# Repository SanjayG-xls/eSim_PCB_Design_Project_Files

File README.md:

<p align="center">
  
</p>

<p align="center">

</p>

## 📋 Table of Contents

- [About the Project](#-about-the-project)
- [STM32F4VE Hardware Overview](#-stm32f4ve-hardware-overview)
- [Software & Toolchain](#-software--toolchain)
- [Hardware Specifications](#-hardware-specifications--features)
- [PCB Stackup & Layer Configuration](#-pcb-stackup--layer-configuration)
- [3D Board Renders](#-3d-board-renders)
- [Schematic Design](#-schematic-design)
- [PCB Layout Views](#-pcb-layout-views)
- [Design Verification](#-design-verification)
- [How to Use](#-how-to-use-this-repository)
- [Video Walkthrough](#-video-walkthrough)
- [Attribution](#-attribution)

## 🔬 About the Project

> 🏛️ **FOSSEE Autumn Internship 2026 — Screening Task**
>
> 
> 
> 
> 
> 

This repository contains the **complete printed circuit board design and schematic files** for an STM32F4VE microcontroller development board. The design was developed as part of the screening task for the **FOSSEE Autumn Internship program in 2026** at **IIT Bombay**.

The core of this board is the high-performance **STM32F407VET6** IC, providing a robust hardware platform for advanced microelectronics and circuit design applications. The board features a **black solder mask** to replicate standard commercial STM development boards, with **custom silkscreen graphics** featuring the official FOSSEE logo, the STM logo, and the designer's name.

## 🧠 STM32F4VE Hardware Overview

The **STM32F4VE** (STM32F407VET6) is a powerful, high-performance **ARM Cortex-M4** core device widely used in embedded systems due to its balance of processing power, memory, and rich peripheral set.

<table>
<tr>
<td width="50%">

### ⚙️ Core Specifications

| Parameter | Value |
|:---|:---|
| **Processor** | ARM 32-bit Cortex-M4 with FPU |
| **Max Frequency** | 168 MHz |
| **Flash Memory** | 512 KB |
| **SRAM** | 192 KB + 4 KB backup |
| **Operating Voltage** | 1.8V – 3.6V |
| **Package** | LQFP-100 |

</td>
<td width="50%">

### 🔌 Advanced Peripherals

| Interface | Count |
|:---|:---|
| **I2C** | Up to 3x |
| **SPI** | Up to 3x |
| **I2S** | Up to 2x |
| **USART / UART** | 4x USART + 2x UART |
| **CAN Bus** | 2x |
| **SDIO** | 1x |

</td>
</tr>
</table>

<p align="center">
  
  <br/>
  <sub><b>STM32F407VET6 — Reference Development Board</b></sub>
</p>

## 🛠️ Software & Toolchain

<table>
<tr>
  <td align="center" width="160">
    
    <br/><sub><b>Schematic Design</b></sub>
  </td>
  <td align="center" width="160">
    
    <br/><sub><b>PCB Layout</b></sub>
  </td>
  <td align="center" width="160">
    
    <br/><sub><b>3D Models / Symbols / Footprints</b></sub>
  </td>
  <td align="center" width="160">
    
    <br/><sub><b>Manufacturing Rules</b></sub>
  </td>
</tr>
</table>

> 📌 **Note:** Schematic design was done in **eSim 2.5**, with PCB layout handled by **KiCad 6** (integrated via eSim). All component libraries — 3D models, schematic symbols, and footprints — were sourced from **SnapEDA**.

## ⚡ Hardware Specifications & Features

> 🔧 **Key Features at a Glance**
>
> 
> 
> 
> 
> 

<table>
<tr>
  <td width="50%" valign="top">

  ### 🎛️ Board Features

  | Feature | Description |
  |:---|:---|
  | **Microcontroller** | STM32F407VET6 high-speed MCU |
  | **Power Management** | 3.3V power routing with CR12 backup battery |
  | **Connectivity** | Micro USB port, SD Card reader |
  | **Headers** | Extensive connector headers for GPIO access |
  | **Timing** | Onboard oscillators for accurate clocking |
  | **User Interface** | Integrated switches and status LEDs |

  </td>
  <td width="50%" valign="top">

  ### 🏭 Manufacturing Specs

  | Parameter | Value |
  |:---|:---|
  | **Layer Count** | 4-Layer PCB |
  | **Manufacturer** | JLCPCB (base model rules) |
  | **Solder Mask** | Black (commercial-grade) |
  | **Silkscreen** | Custom graphics (FOSSEE + STM logos) |
  | **ERC Status** | ✅ Passed (0 errors) |
  | **DRC Status** | ✅ Passed (0 errors) |

  </td>
</tr>
</table>

## 🧱 PCB Stackup & Layer Configuration

The board is routed as a **4-layer PCB**, specifically configured to comply with **JLCPCB base model** manufacturing rules.

<table>
<tr>
  <th align="center">Layer</th>
  <th align="center">Name</th>
  <th align="center">Function</th>
</tr>
<tr>
  <td align="center">🔴 Layer 1</td>
  <td align="center"><b>Front (F.Cu)</b></td>
  <td>Signal routing and ground pour</td>
</tr>
<tr>
  <td align="center">🟡 Layer 2</td>
  <td align="center"><b>Inner 1 (In1.Cu)</b></td>
  <td>Dedicated ground plane</td>
</tr>
<tr>
  <td align="center">🟢 Layer 3</td>
  <td align="center"><b>Inner 2 (In2.Cu)</b></td>
  <td>Dedicated 3.3V power plane</td>
</tr>
<tr>
  <td align="center">🔵 Layer 4</td>
  <td align="center"><b>Back (B.Cu)</b></td>
  <td>Ground plane</td>
</tr>
</table>

<table>
<tr>
  <td align="center" width="50%">
    <b>📐 Layer 1 — Front Copper</b><br/>
    
  </td>
  <td align="center" width="50%">
    <b>📐 Layer 2 — Inner Ground Plane</b><br/>
    
  </td>
</tr>
<tr>
  <td align="center" width="50%">
    <b>📐 Layer 3 — Inner Power Plane (3.3V)</b><br/>
    
  </td>
  <td align="center" width="50%">
    <b>📐 Layer 4 — Back Copper</b><br/>
    
  </td>
</tr>
</table>

<details>
<summary><b>🔍 Click to view individual PCB layer renders</b></summary>
<br/>

<table>
<tr>
  <td align="center" width="50%">
    <b>Front Layer PCB</b><br/>
    
  </td>
  <td align="center" width="50%">
    <b>Back Layer PCB</b><br/>
    
  </td>
</tr>
<tr>
  <td align="center" width="50%">
    <b>Inner Layer 1 (In1.Cu)</b><br/>
    
  </td>
  <td align="center" width="50%">
    <b>Inner Layer 2 (In2.Cu)</b><br/>
    
  </td>
</tr>
</table>

<table>
<tr>
  <td align="center" width="50%">
    <b>All Layers Combined</b><br/>
    
  </td>
  <td align="center" width="50%">
    <b>All ICs Highlighted</b><br/>
    
  </td>
</tr>
</table>

</details>

## 🖼️ 3D Board Renders

<table>
<tr>
  <td align="center" width="50%">
    <b>🔝 Front View — 3D Render</b><br/>
    
  </td>
  <td align="center" width="50%">
    <b>🔽 Back View — 3D Render</b><br/>
    
  </td>
</tr>
<tr>
  <td align="center" width="50%">
    <b>📐 Side View — 3D Render</b><br/>
    
  </td>
  <td align="center" width="50%">
    <b>📐 Side Down View — 3D Render</b><br/>
    
  </td>
</tr>
</table>

<details>
<summary><b>🔍 Click to view additional 3D renders</b></summary>
<br/>

<table>
<tr>
  <td align="center" width="50%">
    <b>3D Model Overview</b><br/>
    
  </td>
  <td align="center" width="50%">
    <b>Front — IC Close-up</b><br/>
    
  </td>
</tr>
<tr>
  <td align="center" width="50%">
    <b>Components Only View</b><br/>
    
  </td>
  <td align="center" width="50%">
    <b>PCB — Components Only (Alt)</b><br/>
    
  </td>
</tr>
</table>

</details>

## 📐 Schematic Design

<p align="center">
  
  <br/>
  <sub><b>Full Schematic Overview — eSim 2.5</b></sub>
</p>

<details>
<summary><b>🔍 Click to view schematic sections</b></summary>
<br/>

<table>
<tr>
  <td align="center" width="50%">
    <b>Schematic — Section 1</b><br/>
    
  </td>
  <td align="center" width="50%">
    <b>Schematic — Section 2</b><br/>
    
  </td>
</tr>
</table>

</details>

## 🔧 PCB Layout Views

<table>
<tr>
  <td align="center" width="50%">
    <b>📋 PCB — All Layers</b><br/>
    
  </td>
  <td align="center" width="50%">
    <b>📋 JLCPCB Gerber Preview</b><br/>
    
  </td>
</tr>
</table>

## ✅ Design Verification

<table>
<tr>
  <td align="center" width="50%">
    <b>🔋 ERC — Electrical Rules Check</b><br/>
    
  </td>
  <td align="center" width="50%">
    <b>📏 DRC — Design Rules Check</b><br/>
    
  </td>
</tr>
</table>

> ✅ **Electrical Rules Check (ERC):** Passed with **zero errors**. Wire labels were utilized for power nets instead of standard power flags.
>
> ✅ **Design Rules Check (DRC):** Passed with **zero errors**, ensuring complete manufacturability compliance with JLCPCB specifications.

<details>
<summary><b>🔍 Click to view additional verification results</b></summary>
<br/>

<table>
<tr>
  <td align="center" width="50%">
    <b>DRC — PCB View</b><br/>
    
  </td>
  <td align="center" width="50%">
    <b>Excluded ERC Warnings</b><br/>
    
  </td>
</tr>
</table>

</details>

## 📦 How to Use This Repository

```
1.  Download the project repository and extract the files.
2.  Open the schematic files using eSim 2.5 to view circuit connections.
3.  Open the PCB layout files in KiCad 6 to inspect:
      • Routing and trace widths
      • Layer stackup configuration
      • 3D model and component placement
4.  Generate Gerber files directly from KiCad for fabrication
    at any standard PCB manufacturer (JLCPCB recommended).
```

> 💡 **Tip:** All component libraries (3D models, symbols, footprints) are sourced from [SnapEDA](https://www.snapeda.com/) and should be imported into your KiCad library manager before editing.

## 🎬 Video Walkthrough

<p align="center">
  
</p>

<p align="center">
  
  <br/>
  <sub><b>📹 Click to watch the complete project walkthrough on YouTube</b></sub>
</p>

## 🏷️ Attribution

<table>
<tr>
  <td align="center" width="33%">
    
    <br/><sub><b>Program Host</b></sub>
  </td>
  <td align="center" width="33%">
    
    <br/><sub><b>PCB Design & Schematics</b></sub>
  </td>
  <td align="center" width="33%">
    
    <br/><sub><b>Component Sources</b></sub>
  </td>
</tr>
</table>

<p align="center">
  <sub>⭐ Star this repo if you found it useful! ⭐</sub>
</p>

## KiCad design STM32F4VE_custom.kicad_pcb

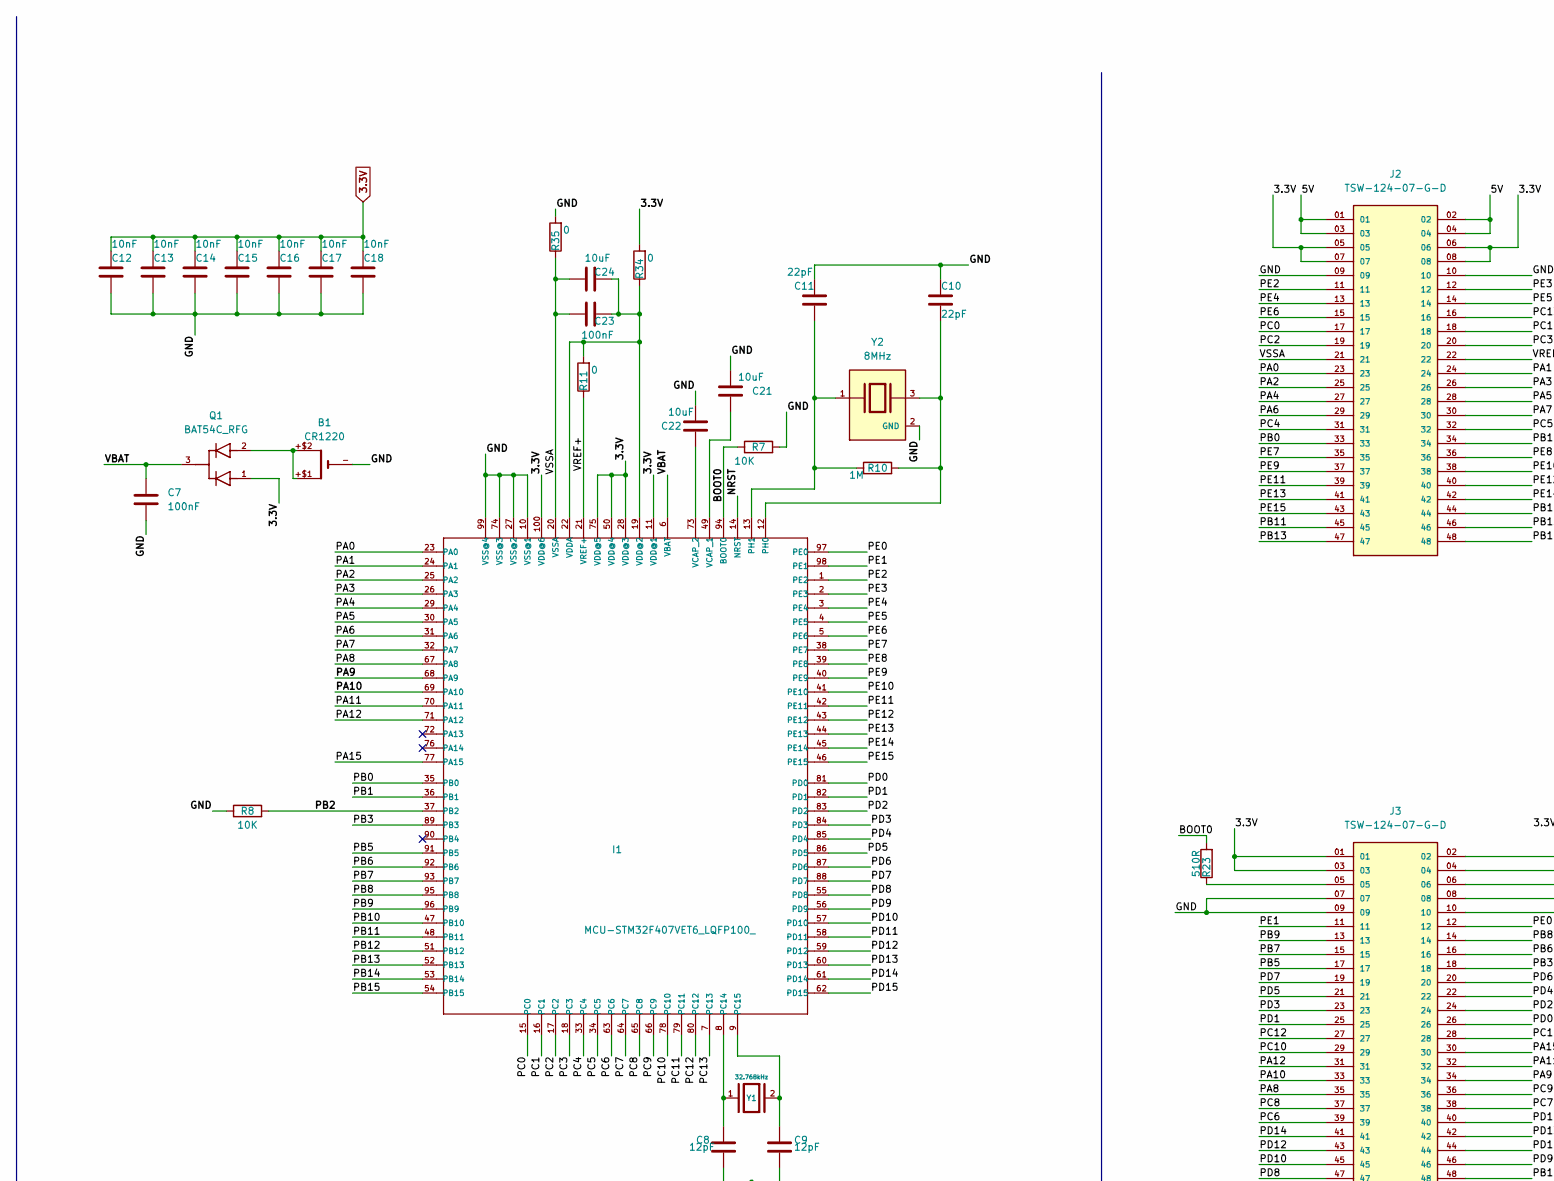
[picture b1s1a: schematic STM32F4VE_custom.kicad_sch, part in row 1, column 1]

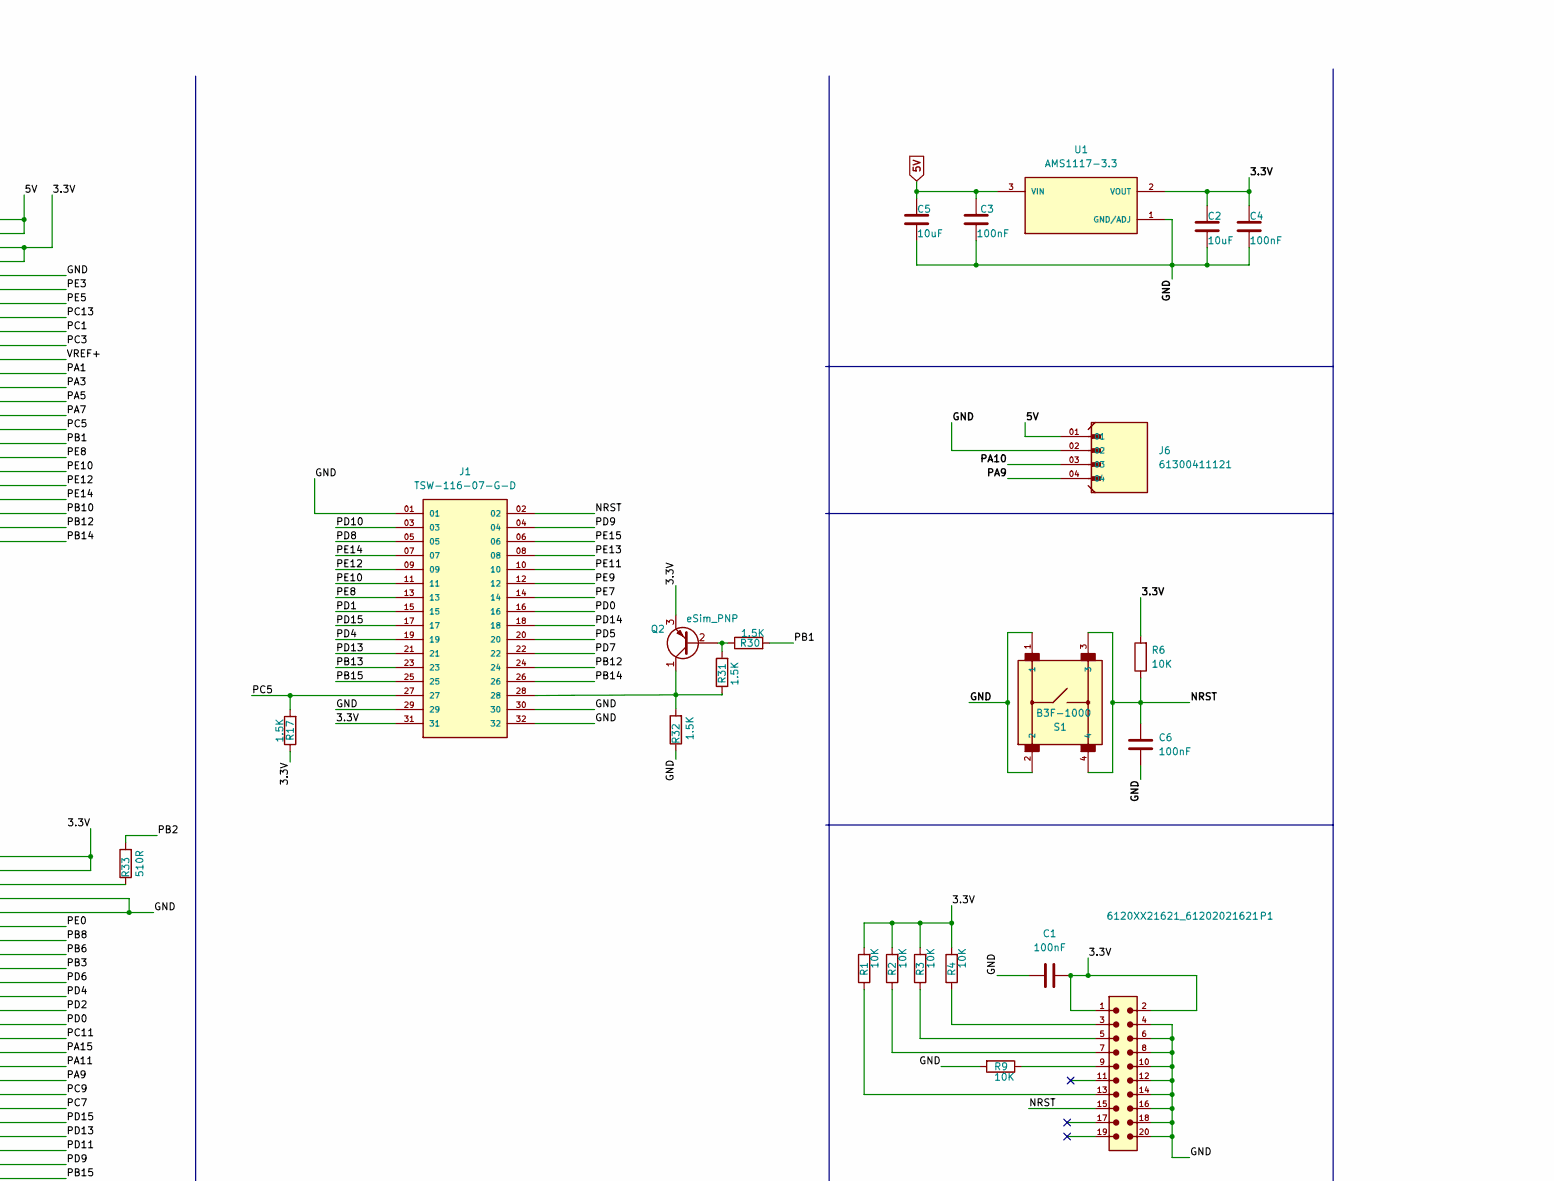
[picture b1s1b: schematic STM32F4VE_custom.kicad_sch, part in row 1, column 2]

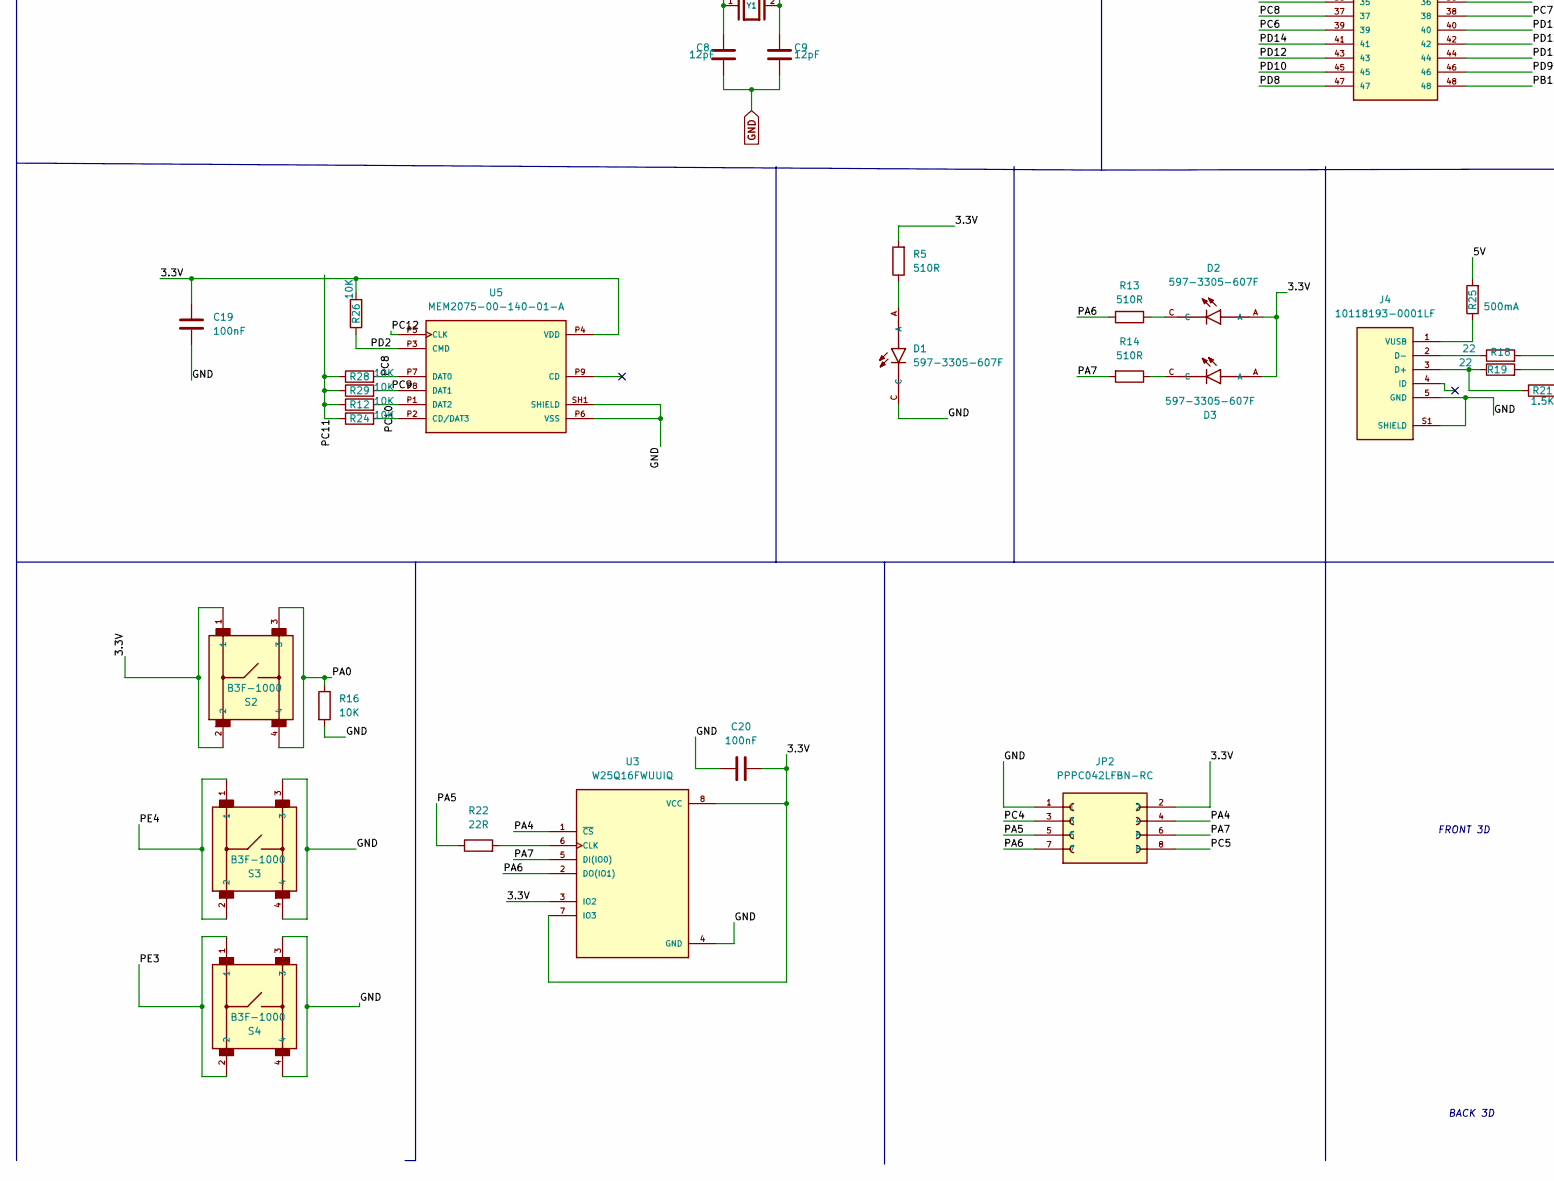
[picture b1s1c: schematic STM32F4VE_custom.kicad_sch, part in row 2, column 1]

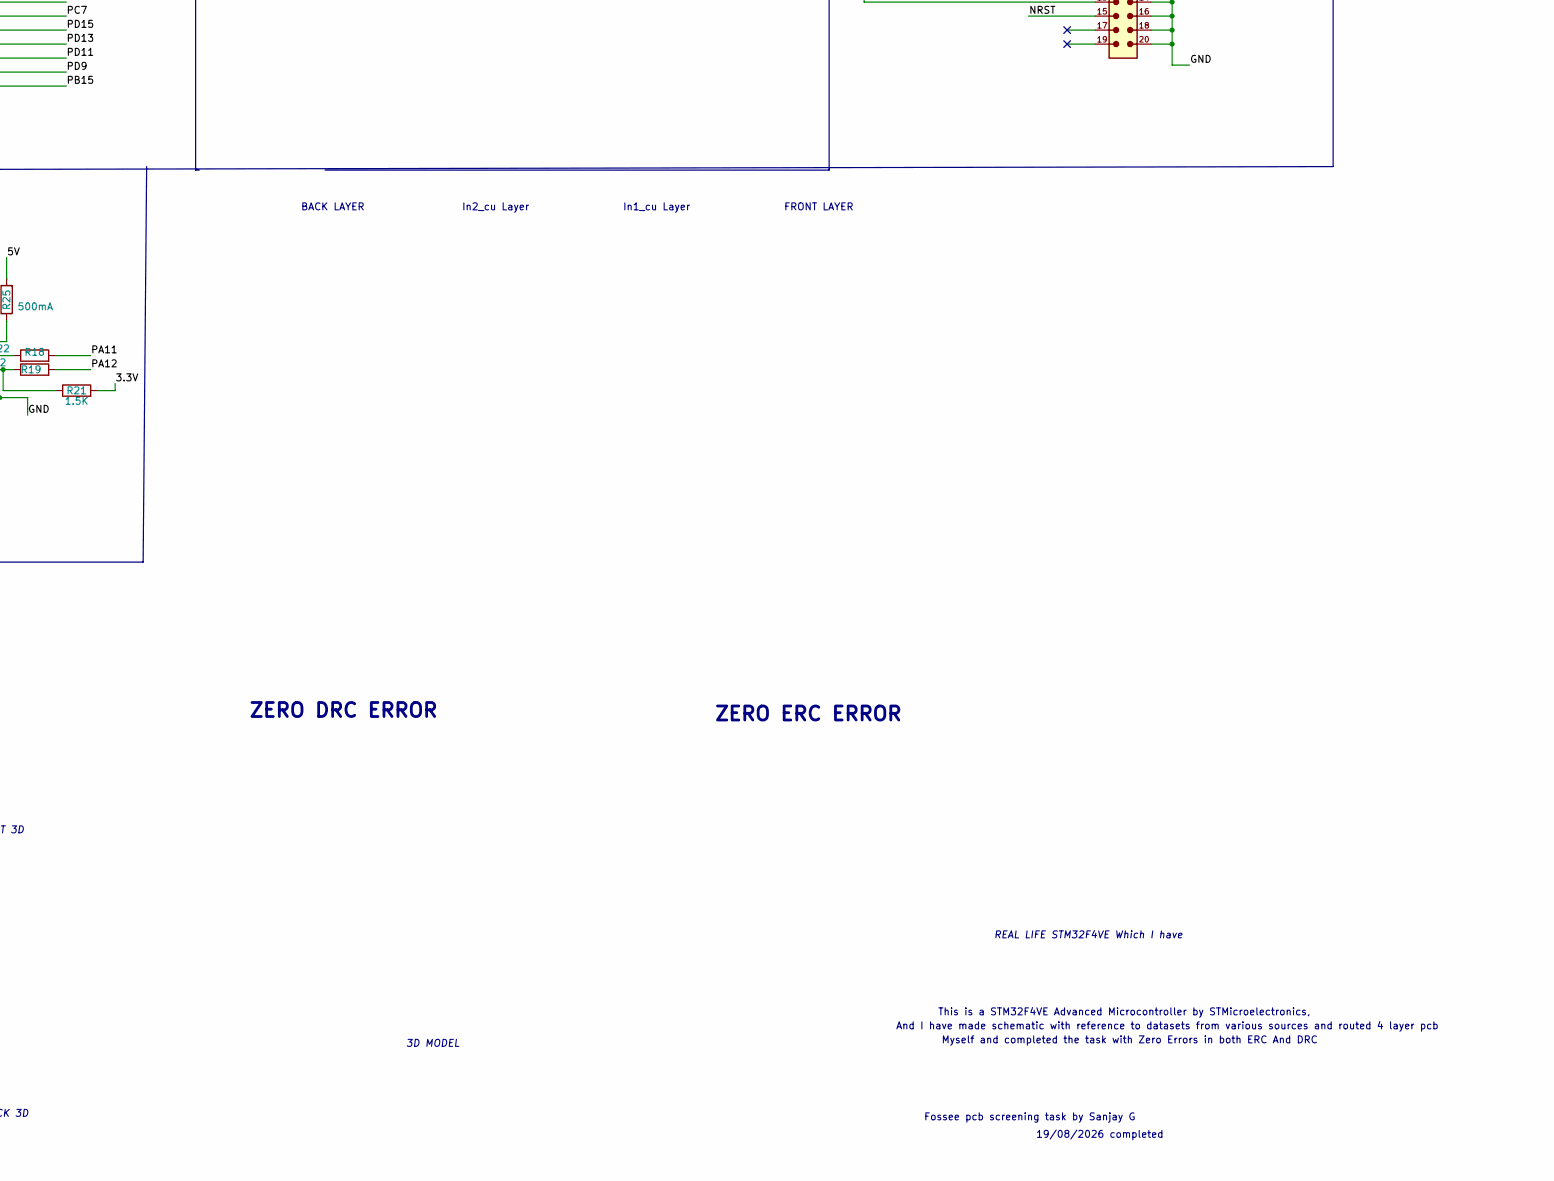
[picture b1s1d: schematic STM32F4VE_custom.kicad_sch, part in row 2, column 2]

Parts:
B1: CR1220; CR1220-SMD
C1, C3, C4, C6, C7, C19, C20, C23: 100nF; C_0805_2012Metric_Pad1.18x1.45mm_HandSolder
C2, C5, C21, C22, C24: 10uF; C_0805_2012Metric_Pad1.18x1.45mm_HandSolder
C8, C9: 12pF; C_0805_2012Metric_Pad1.18x1.45mm_HandSolder
C10, C11: 22pF; C_0805_2012Metric_Pad1.18x1.45mm_HandSolder
C12, C13, C14, C15, C16, C17, C18: 10nF; C_0805_2012Metric_Pad1.18x1.45mm_HandSolder
D1, D2, D3: 597-3305-607F; LEDC2012X70N
I1: MCU-STM32F407VET6_LQFP100_; LQFP100-0.5-13.8X13.8MM; MPN STM32F407VET6
J1: TSW-116-07-G-D; SAMTEC_TSW-116-07-G-D; PARTREV R
J2, J3: TSW-124-07-G-D; SAMTEC_TSW-124-07-G-D; PARTREV R
J4: 10118193-0001LF; AMPHENOL_10118193-0001LF; PARTREV E
J6: 61300411121; WURTH_61300411121
JP2: PPPC042LFBN-RC; SULLINS_PPPC042LFBN-RC; PARTREV L
P1: 6120XX21621_61202021621; 61202021621
Q1: BAT54C_RFG; SOT95P237X112-3N; PARTREV E2001
Q2: eSim_PNP; SOT-23
R1, R2, R3, R4, R6, R7, R8, R9, R12, R16, R24, R26, R28, R29: 10K; R_1206_3216Metric
R5, R13, R14, R23, R33: 510R; R_1206_3216Metric
R10: 1M; R_1206_3216Metric
R11, R34, R35: 0; R_1206_3216Metric
R17, R21, R30, R31, R32: 1.5K; R_1206_3216Metric
R18, R19: 22; R_1206_3216Metric
R22: 22R; R_1206_3216Metric
R25: 500mA; R_1206_3216Metric
S1, S2, S3, S4: B3F-1000; SW_B3F-1000
U1: AMS1117-3.3; SOT-223-3_TabPin2; PARTREV N/A
U3: W25Q16FWUUIQ; SON80P400X300X60-8N; PARTREV J
U5: MEM2075-00-140-01-A; GCT_MEM2075-00-140-01-A; PARTREV A
Y1: 32.768kHz; XTAL_ABS07-32.768KHZ-T; PARTREV 08.19.15
Y2: 8MHz; Crystal_SMD_3225-4Pin_3.2x2.5mm; PARTREV 43629

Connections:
3.3V: C1.2, C2.1, C4.1, C12.1, C13.1, C14.1, C15.1, C16.1, C17.1, C18.1, C19.1, C20.2, D2.A, D3.A, I1.11 (VDD@1), I1.28 (VDD@3), I1.50 (VDD@4), I1.75 (VDD@5), I1.100 (VDD@6), J1.31, J2.05, J2.06, J2.07, J2.08, J3.01, J3.02, J3.03, J3.04, JP2.2, P1.1, P1.2, Q1.1, Q2.3 (E), R1.2, R2.2, R3.2, R4.2, R5.2, R6.2, R17.1, R21.2, R26.2, R34.2, S2.1, S2.2, U1.2 (VOUT), U3.3 (IO2), U3.7 (IO3), U3.8 (VCC), U5.P4 (VDD)
5V: C3.1, C5.1, J2.01, J2.02, J2.03, J2.04, J6.01, R25.2, U1.3 (VIN)
/BOOT0: I1.94 (BOOT0), R7.1, R23.2
/NRST: C6.1, I1.14 (NRST), J1.02, P1.15, R6.1, S1.3, S1.4
/PA0: I1.23 (PA0), J2.23, R16.1, S2.3, S2.4
/PA1: I1.24 (PA1), J2.24
/PA2: I1.25 (PA2), J2.25
/PA3: I1.26 (PA3), J2.26
/PA4: I1.29 (PA4), J2.27, JP2.4, U3.1 (~CS)
/PA5: I1.30 (PA5), J2.28, JP2.5, R22.1
/PA6: I1.31 (PA6), J2.29, JP2.7, R13.2, U3.2 (DO(IO1))
/PA7: I1.32 (PA7), J2.30, JP2.6, R14.2, U3.5 (DI(IO0))
/PA8: I1.67 (PA8), J3.35
/PA9: I1.68 (PA9), J3.34, J6.04
/PA10: I1.69 (PA10), J3.33, J6.03
/PA11: I1.70 (PA11), J3.32, R18.2
/PA12: I1.71 (PA12), J3.31, R19.2
/PA15: I1.77 (PA15), J3.30
/PB0: I1.35 (PB0), J2.33
/PB1: I1.36 (PB1), J2.34, R30.2
/PB2: I1.37 (PB2), R8.2, R33.2
/PB3: I1.89 (PB3), J3.18
/PB5: I1.91 (PB5), J3.17
/PB6: I1.92 (PB6), J3.16
/PB7: I1.93 (PB7), J3.15
/PB8: I1.95 (PB8), J3.14
/PB9: I1.96 (PB9), J3.13
/PB10: I1.47 (PB10), J2.44
/PB11: I1.48 (PB11), J2.45
/PB12: I1.51 (PB12), J1.24, J2.46
/PB13: I1.52 (PB13), J1.23, J2.47
/PB14: I1.53 (PB14), J1.26, J2.48
/PB15: I1.54 (PB15), J1.25, J3.48
/PC0: I1.15 (PC0), J2.17
/PC1: I1.16 (PC1), J2.18
/PC2: I1.17 (PC2), J2.19
/PC3: I1.18 (PC3), J2.20
/PC4: I1.33 (PC4), J2.31, JP2.3
/PC5: I1.34 (PC5), J1.27, J2.32, JP2.8, R17.2
/PC6: I1.63 (PC6), J3.39
/PC7: I1.64 (PC7), J3.38
/PC8: I1.65 (PC8), J3.37, R28.2, U5.P7 (DAT0)
/PC9: I1.66 (PC9), J3.36, R29.2, U5.P8 (DAT1)
/PC10: I1.78 (PC10), J3.29, R12.2, U5.P1 (DAT2)
/PC11: I1.79 (PC11), J3.28, R12.1, R24.1, R28.1, R29.1
/PC12: I1.80 (PC12), J3.27, U5.P5 (CLK)
/PC13: I1.7 (PC13), J2.16
/PD0: I1.81 (PD0), J1.16, J3.26
/PD1: I1.82 (PD1), J1.15, J3.25
/PD2: I1.83 (PD2), J3.24, R26.1, U5.P3 (CMD)
/PD3: I1.84 (PD3), J3.23
/PD4: I1.85 (PD4), J1.19, J3.22
/PD5: I1.86 (PD5), J1.20, J3.21
/PD6: I1.87 (PD6), J3.20
/PD7: I1.88 (PD7), J1.22, J3.19
/PD8: I1.55 (PD8), J1.05, J3.47
/PD9: I1.56 (PD9), J1.04, J3.46
/PD10: I1.57 (PD10), J1.03, J3.45
/PD11: I1.58 (PD11), J3.44
/PD12: I1.59 (PD12), J3.43
/PD13: I1.60 (PD13), J1.21, J3.42
/PD14: I1.61 (PD14), J1.18, J3.41
/PD15: I1.62 (PD15), J1.17, J3.40
/PE0: I1.97 (PE0), J3.12
/PE1: I1.98 (PE1), J3.11
/PE2: I1.1 (PE2), J2.11
/PE3: I1.2 (PE3), J2.12, S4.1, S4.2
/PE4: I1.3 (PE4), J2.13, S3.1, S3.2
/PE5: I1.4 (PE5), J2.14
/PE6: I1.5 (PE6), J2.15
/PE7: I1.38 (PE7), J1.14, J2.35
/PE8: I1.39 (PE8), J1.13, J2.36
/PE9: I1.40 (PE9), J1.12, J2.37
/PE10: I1.41 (PE10), J1.11, J2.38
/PE11: I1.42 (PE11), J1.10, J2.39
/PE12: I1.43 (PE12), J1.09, J2.40
/PE13: I1.44 (PE13), J1.08, J2.41
/PE14: I1.45 (PE14), J1.07, J2.42
/PE15: I1.46 (PE15), J1.06, J2.43
/VBAT: C7.1, I1.6 (VBAT), Q1.3
/VREF+: I1.21 (VREF+), J2.22, R11.1
/VSSA: C23.1, C24.1, I1.20 (VSSA), J2.21, R35.1
GND: B1.-, C1.1, C2.2, C3.2, C4.2, C5.2, C6.2, C7.2, C8.2, C9.2, C10.1, C11.1, C12.2, C13.2, C14.2, C15.2, C16.2, C17.2, C18.2, C19.2, C20.1, C21.1, C22.1, D1.C, I1.10 (VSS@1), I1.27 (VSS@2), I1.74 (VSS@3), I1.99 (VSS@4), J1.01, J1.29, J1.30, J1.32, J2.09, J2.10, J3.07, J3.08, J3.09, J3.10, J4.5 (GND), J4.S1 (SHIELD), J4.S2 (SHIELD), J4.S3 (SHIELD), J4.S4 (SHIELD), J4.S5 (SHIELD), J4.S6 (SHIELD), J6.02, JP2.1, P1.4, P1.6, P1.8, P1.10, P1.12, P1.14, P1.16, P1.18, P1.20, R7.2, R8.1, R9.2, R16.2, R32.1, R35.2, S1.1, S1.2, S3.3, S3.4, S4.3, S4.4, U1.1 (GND/ADJ), U3.4 (GND), U5.P6 (VSS), U5.SH1 (SHIELD), U5.SH2 (SHIELD), U5.SH3 (SHIELD), U5.SH4 (SHIELD), Y2.2 (GND), Y2.4 (GND)
unnamed: B1.+$1, B1.+$2, Q1.2
unnamed: C8.1, I1.8 (PC14), Y1.1
unnamed: C9.1, I1.9 (PC15), Y1.2
unnamed: C10.2, I1.12 (PH0), R10.2, Y2.3
unnamed: C11.2, I1.13 (PH1), R10.1, Y2.1
unnamed: C21.2, I1.49 (VCAP_1)
unnamed: C22.2, I1.73 (VCAP_2)
unnamed: C23.2, C24.2, I1.19 (VDD@2), I1.22 (VDDA), R11.2, R34.1
unnamed: D1.A, R5.1
unnamed: D2.C, R13.1
unnamed: D3.C, R14.1
unnamed: J1.28, Q2.1 (C), R31.1, R32.2
unnamed: J3.05, R23.1
unnamed: J3.06, R33.1
unnamed: J4.1 (VUSB), R25.1
unnamed: J4.2 (D-), R18.1
unnamed: J4.3 (D+), R19.1, R21.1
unnamed: P1.3, R4.1
unnamed: P1.5, R3.1
unnamed: P1.7, R2.1
unnamed: P1.9, R9.1
unnamed: P1.13, R1.1
unnamed: Q2.2 (B), R30.1, R31.2
unnamed: R22.2, U3.6 (CLK)
unnamed: R24.2, U5.P2 (CD/DAT3)

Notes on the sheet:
In2_cu Layer
BACK LAYER
REAL LIFE STM32F4VE Which I have
ZERO ERC ERROR
And I have made schematic with reference to datasets from various sources and routed 4 layer pcb
This is a STM32F4VE Advanced Microcontroller by STMicroelectronics,
BACK 3D
19/08/2026 completed
FRONT 3D
FRONT LAYER
3D MODEL
ZERO DRC ERROR
Myself and completed the task with Zero Errors in both ERC And DRC
In1_cu Layer
Fossee pcb screening task by Sanjay G

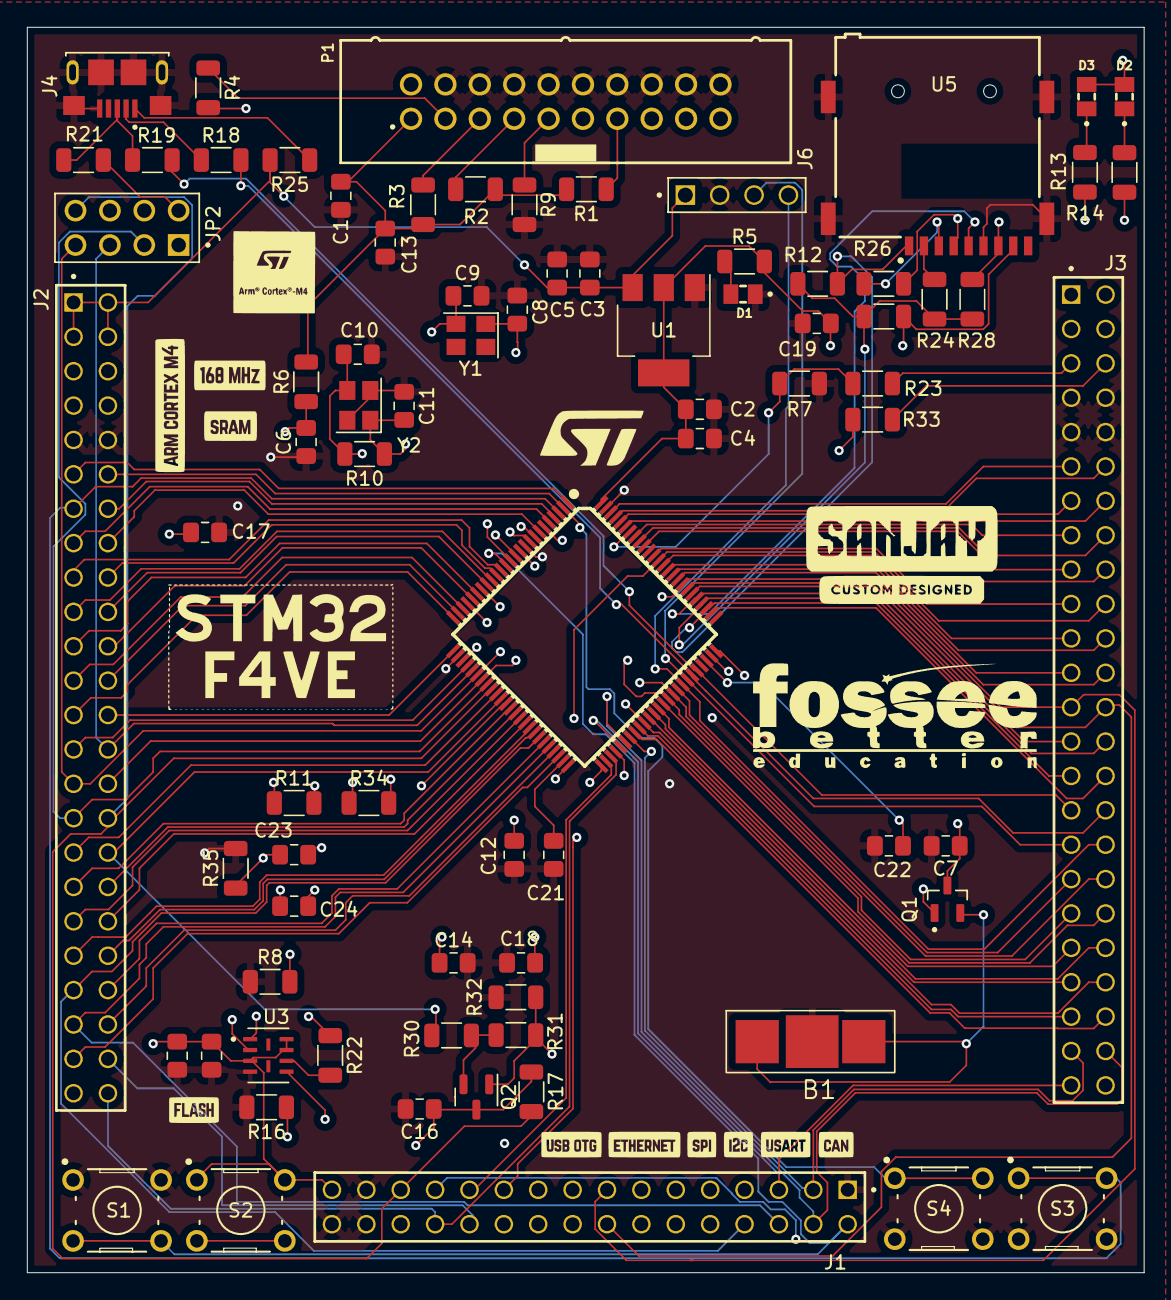
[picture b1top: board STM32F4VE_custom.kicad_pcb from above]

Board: 4 copper layers, 82.5 x 92.0 mm, 79 parts (0 on the bottom side), 108 nets.

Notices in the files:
README.md:
License: MIT
